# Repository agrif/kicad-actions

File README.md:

# KiCad Actions

*GitHub Actions for KiCad designs.*

More info here later.

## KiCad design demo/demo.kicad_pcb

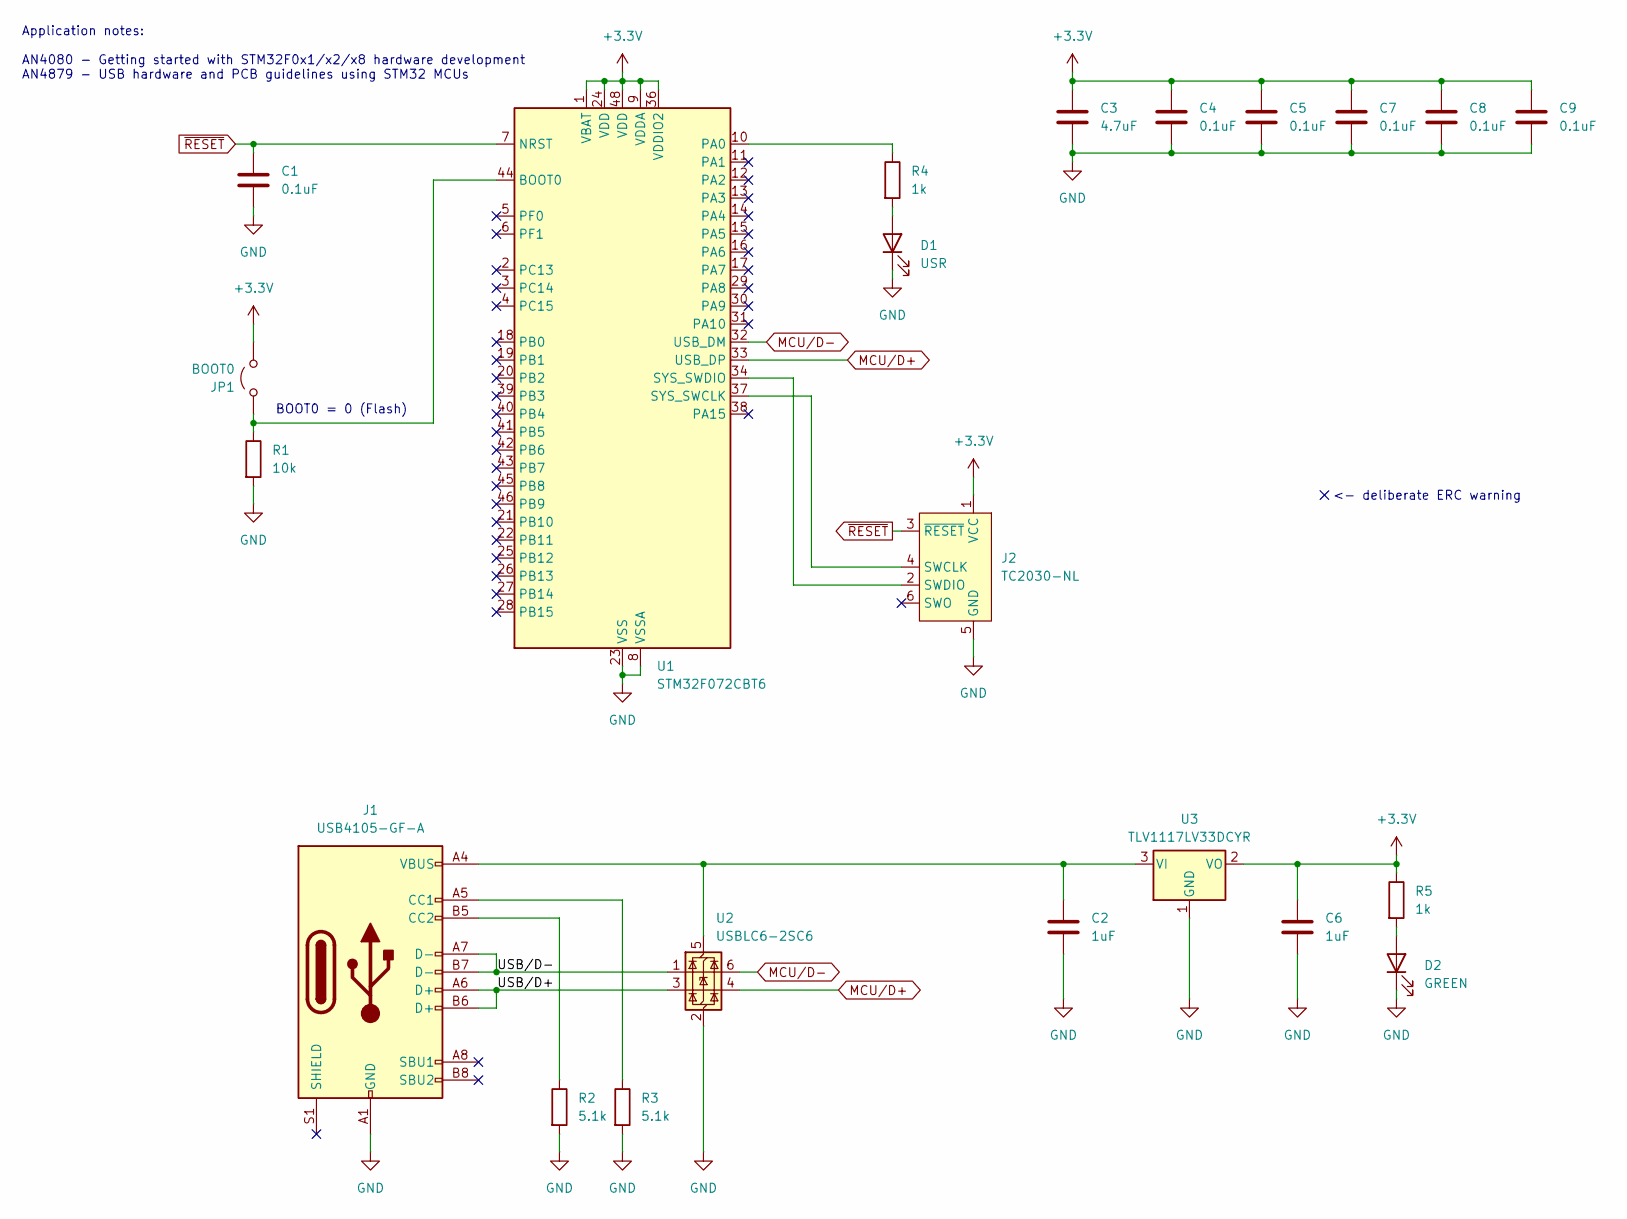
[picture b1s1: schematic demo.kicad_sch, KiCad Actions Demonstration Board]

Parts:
C1, C4, C5, C7, C8, C9: 0.1uF; C_0603_1608Metric; Mouser 603-CC603KRX7R9BB104
C2, C6: 1uF; C_0603_1608Metric; Mouser 603-CC603KRX7R7BB105
C3: 4.7uF; C_0603_1608Metric; Mouser 603-CC603KRX5R7BB475
D1: USR; D_1206_3216Metric; Mouser 710-156120VS75000
D2: GREEN; D_1206_3216Metric; Mouser 710-156120VS75000
J1: USB4105-GF-A; USB_C_Receptacle_GCT_USB4105-xx-A_16P_TopMnt_Horizontal; Mouser 640-USB4105-GF-A
J2: TC2030-NL; Tag-Connect_TC2030-IDC-NL_2x03_P1.27mm_Vertical
JP1: BOOT0; PinHeader_1x02_P2.54mm_Vertical
R1: 10k; R_0603_1608Metric; Mouser 603-RT0603DRD0710KL
R2, R3: 5.1k; R_0603_1608Metric; Mouser 603-RT0603DRD075K1L
R4, R5: 1k; R_0603_1608Metric; Mouser 603-RT0603DRE071KL
U1: STM32F072CBT6; LQFP-48_7x7mm_P0.5mm; Mouser 511-STM32F072CBT6
U2: USBLC6-2SC6; SOT-23-6; Mouser 511-USBLC6-2SC6
U3: TLV1117LV33DCYR; SOT-223-3_TabPin2; Mouser 595-TLV1117LV33DCYR

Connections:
+3.3V: C3.1, C4.1, C5.1, C6.1, C7.1, C8.1, C9.1, J2.1 (VCC), JP1.2 (B), R5.1, U1.1 (VBAT), U1.9 (VDDA), U1.24 (VDD), U1.36 (VDDIO2), U1.48 (VDD), U3.2 (VO)
/USB/D+: J1.A6 (D+), J1.B6 (D+), U2.3 (I/O2)
/USB/D-: J1.A7 (D-), J1.B7 (D-), U2.1 (I/O1)
GND: C1.2, C2.2, C3.2, C4.2, C5.2, C6.2, C7.2, C8.2, C9.2, D1.1 (K), D2.1 (K), J1.A1 (GND), J1.A12 (GND), J1.B1 (GND), J1.B12 (GND), J2.5 (GND), R1.2, R2.2, R3.2, U1.8 (VSSA), U1.23 (VSS), U1.35 (VSS), U1.47 (VSS), U2.2 (GND), U3.1 (GND)
MCU/D+: U1.33 (USB_DP), U2.4 (I/O2)
MCU/D-: U1.32 (USB_DM), U2.6 (I/O1)
unnamed: D1.2 (A), R4.2
unnamed: D2.2 (A), R5.2
unnamed: J1.A5 (CC1), R3.1
unnamed: J1.B5 (CC2), R2.1
unnamed: J2.4 (SWCLK), U1.37 (SYS_SWCLK)
unnamed: J2.2 (SWDIO), U1.34 (SYS_SWDIO)
unnamed: JP1.1 (A), R1.1, U1.44 (BOOT0)
unnamed: R4.1, U1.10 (PA0)
unnamed: C2.1, J1.A4 (VBUS), J1.A9 (VBUS), J1.B4 (VBUS), J1.B9 (VBUS), U2.5 (VBUS), U3.3 (VI)
~RESET: C1.1, J2.3 (~RESET), U1.7 (NRST)

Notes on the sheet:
<- deliberate ERC warning
BOOT0 = 0 (Flash)
Application notes: AN4080 - Getting started with STM32F0x1/x2/x8 hardware development AN4879 - USB hardware and PCB guidelines using STM32 MCUs

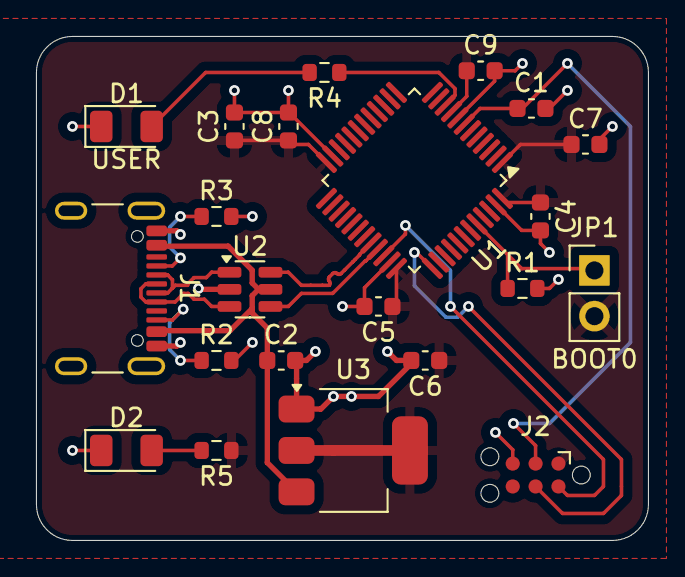
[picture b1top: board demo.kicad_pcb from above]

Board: 2 copper layers, 34.0 x 28.0 mm, 22 parts (0 on the bottom side), 16 nets.

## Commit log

2025-04-09 python tool to find kicad files and do erc/drc reports
2025-04-09 initial version of setup action
2025-04-09 print kicad version info in setup
2025-04-09 initial version of erc
2025-04-09 copy library tables in setup
2025-04-09 separate formatting from erc so we can save the json report also
2025-04-09 add python3 and python3-click to install step
2025-04-09 add drc action
2025-04-09 move formatted drc/erc to step summary
2025-04-11 add a pcb render preview
2025-04-11 put outputs into an artifact
2025-04-11 add schematic action
2025-04-11 apparently we need explicit outputs
